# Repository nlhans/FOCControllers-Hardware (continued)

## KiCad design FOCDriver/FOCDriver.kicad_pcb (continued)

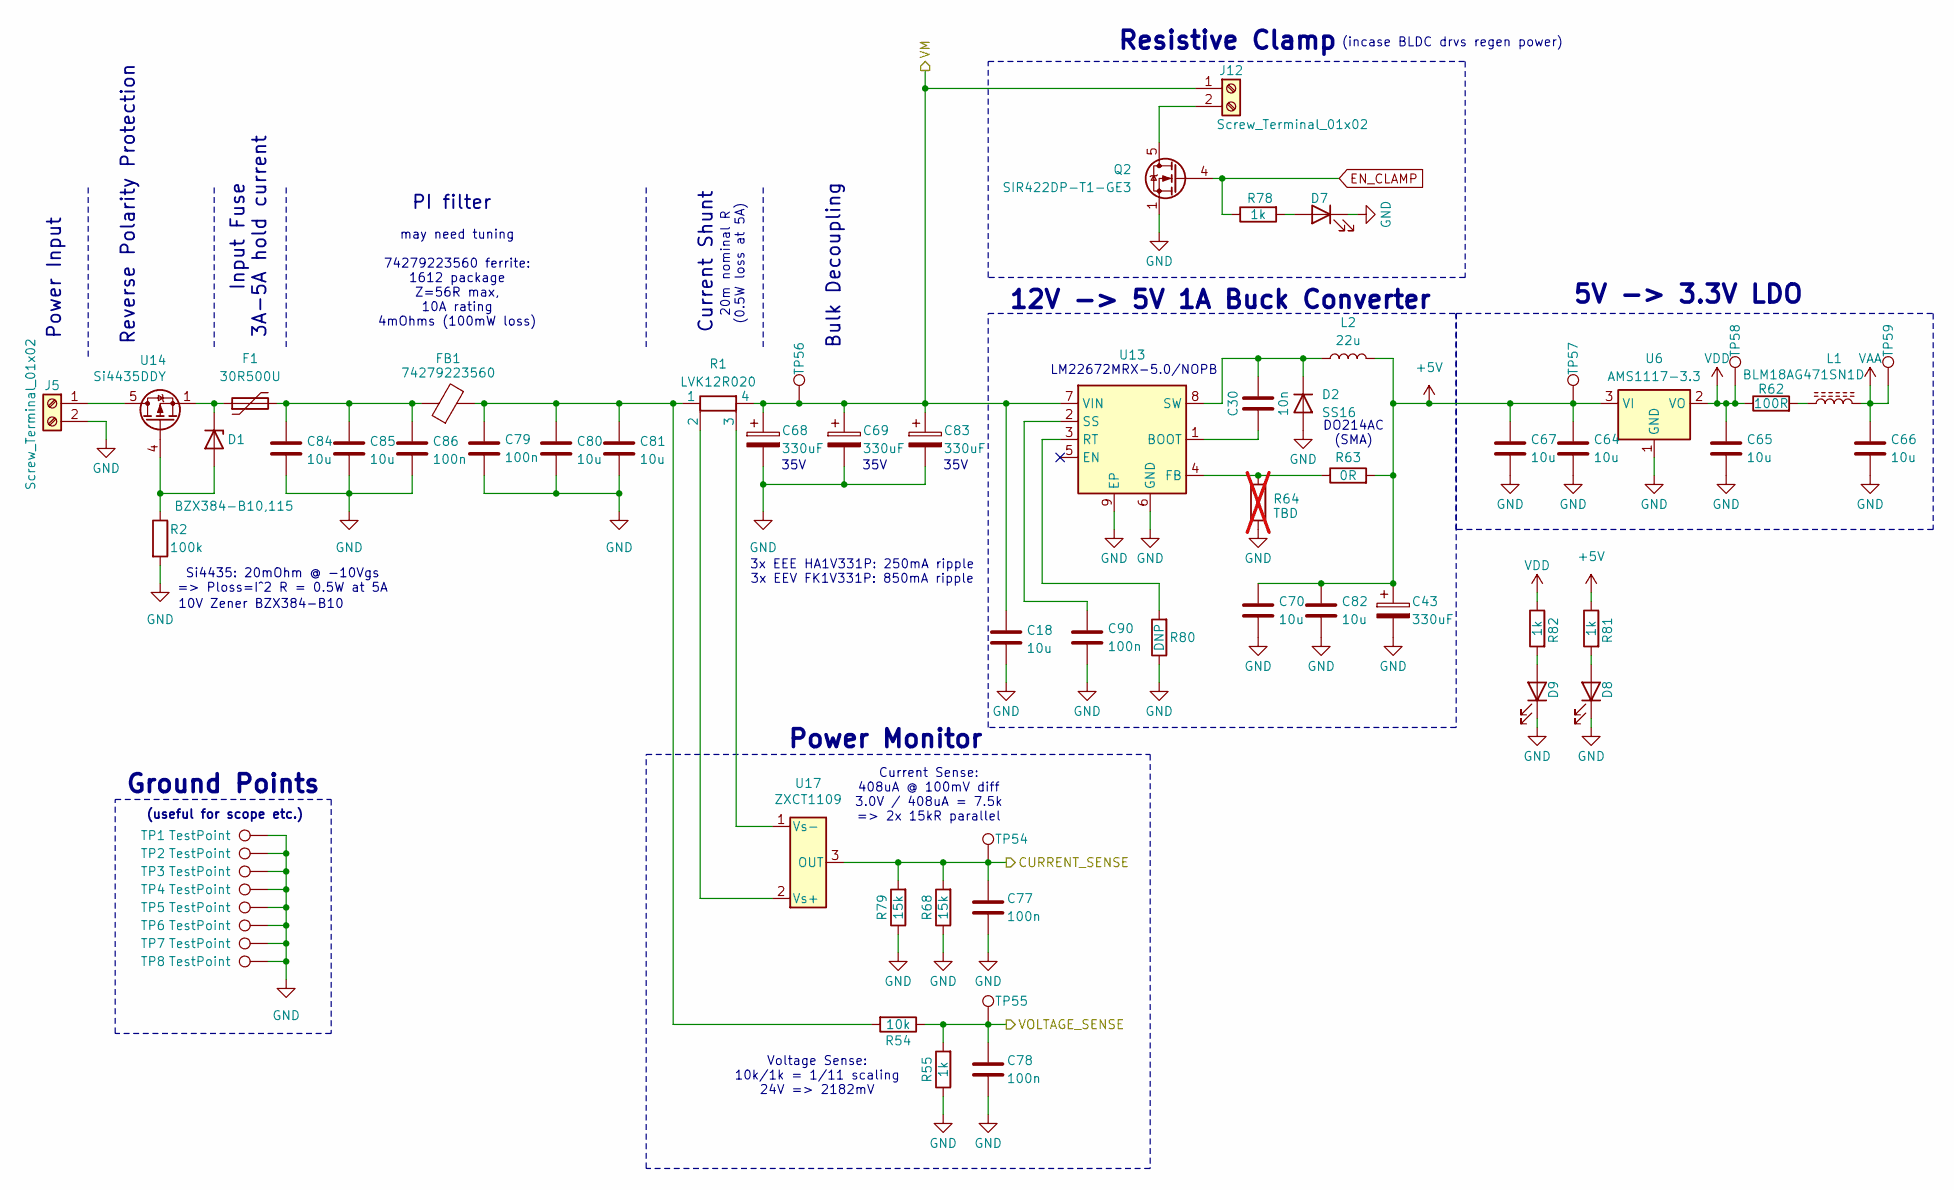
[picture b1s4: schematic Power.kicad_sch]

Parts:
C18, C64, C65, C66, C67, C70, C80, C81, C82, C84, C85: 10u; C_1206_3216Metric
C30: 10n; Nice_0603C
C43: 330uF; CP_Elec_8x10.5; MPN EEEFT1V331AP
C68, C69, C83: 330uF; CP_Elec_10x10.5; MPN EEV FK1V331P
C77, C78: 100n; Nice_0402C
C79, C86, C90: 100n; Nice_0603C
D1: BZX384-B10,115; D_SOD-323_HandSoldering; MPN BZX384-B10,115
D2: SS16; D_SMA
D7, D8, D9: APT2012SYCK; LED_0805_2012Metric; MPN APT2012SYCK
F1: 30R500U; LIttelfuse_30R
FB1: 74279223560; L_1812_4532Metric
J5, J12: Screw_Terminal_01x02; TerminalBlock_Phoenix_MKDS-1,5-2_1x02_P5.00mm_Horizontal
L1: BLM18AG471SN1D; L_0805_2012Metric
L2: 22u; L_Bourns-SRN8040_8x8.15mm; MPN SRN8040-220M
Q2: SIR422DP-T1-GE3; PowerPAK_SO-8_Single
R1: LVK12R020; R_Shunt_Ohmite_LVK12; MPN LVK12R020CER
R2: 100k; Nice_0402R
R54: 10k; Nice_0402R
R55, R78, R81, R82: 1k; Nice_0402R
R62: 100R; Nice_0402R
R63: 0R; Nice_0402R
R64: TBD; Nice_0402DNP; not fitted
R68, R79: 15k; Nice_0402R
R80: DNP; Nice_0402DNP
TP1, TP2, TP3, TP4, TP5, TP6, TP7, TP8: TestPoint; TestPoint_THTPad_D1.0mm_Drill0.5mm
TP54, TP55, TP56, TP57, TP58, TP59: TestPoint; TP_0.6mm
U6: AMS1117-3.3; SOT-223-3_TabPin2
U13: LM22676MR-5; TI_SO-PowerPAD-8; MPN LM22672MRX-5.0/NOPB
U14: Si4435DDY; SOIC-8_3.9x4.9mm_P1.27mm
U17: ZXCT1109; SOT-23; MPN ZXCT1109SA-7

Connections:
+5V: C43.1, C64.1, C67.1, C70.1, C82.1, L2.2, R63.2, R81.1, TP57.1, U6.3 (VI); also elsewhere on the board
/MCU/AIN_I: C77.1, R68.2, R79.2, TP54.1, U17.3 (OUT); also elsewhere on the board
/MCU/AIN_V: C78.1, R54.1, R55.2, TP55.1; also elsewhere on the board
/Motor1/VM: C18.1, C68.1, C69.1, C83.1, J12.1, R1.4, TP56.1, U13.7 (VIN); also elsewhere on the board
EN_CLAMP: Q2.4 (G), R78.1; also elsewhere on the board
GND: C18.2, C43.2, C64.2, C65.2, C66.2, C67.2, C68.2, C69.2, C70.2, C77.2, C78.2, C79.2, C80.2, C81.2, C82.2, C83.2, C84.2, C85.2, C86.2, C90.2, D2.2 (A), D7.1 (K), D8.1 (K), D9.1 (K), J5.2, Q2.1 (S), Q2.2 (S), Q2.3 (S), R2.2, R55.1, R64.2, R68.1, R79.1, R80.1, TP1.1, TP2.1, TP3.1, TP4.1, TP5.1, TP6.1, TP7.1, TP8.1, U6.1 (GND), U13.6 (GND), U13.9 (EP); also elsewhere on the board
unnamed: C79.1, C80.1, C81.1, FB1.2, R1.1, R54.2
unnamed: C84.1, C85.1, C86.1, F1.2, FB1.1
unnamed: D1.2 (A), R2.1, U14.4 (G)
unnamed: D1.1 (K), F1.1, U14.1 (S), U14.2 (S), U14.3 (S)
unnamed: C30.2, D2.1 (K), L2.1, U13.8 (SW)
unnamed: D7.2 (A), R78.2
unnamed: D8.2 (A), R81.2
unnamed: D9.2 (A), R82.2
unnamed: J5.1, U14.5 (D), U14.6 (D), U14.7 (D), U14.8 (D)
unnamed: J12.2, Q2.5 (D)
unnamed: L1.1, R62.2
unnamed: C30.1, U13.1 (BOOT)
unnamed: R63.1, R64.1, U13.4 (FB)
unnamed: R80.2, U13.3 (RT)
unnamed: C90.1, U13.2 (SS)
unnamed: R1.2, U17.2 (Vs+)
unnamed: R1.3, U17.1 (Vs-)
VAA: C66.1, L1.2, TP59.1; also elsewhere on the board
VDD: C65.1, R62.1, R82.1, TP58.1, U6.2 (VO); also elsewhere on the board

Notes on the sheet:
(useful for scope etc.)
Current Shunt
DO214AC (SMA)
may need tuning 74279223560 ferrite: 1612 package Z=56R max, 10A rating 4mOhms (100mW loss)
35V
3x EEE HA1V331P: 250mA ripple 3x EEV FK1V331P: 850mA ripple
(incase BLDC drvs regen power)
Power Input
Input Fuse 3A-5A hold current
Resistive Clamp
Power Monitor
LM22672MRX-5.0/NOPB
Bulk Decoupling
Ground Points
10V Zener BZX384-B10
12V -> 5V 1A Buck Converter
Voltage Sense: 10k/1k = 1/11 scaling 24V => 2182mV
Si4435: 20mOhm @ -10Vgs => Ploss=I^2 R = 0.5W at 5A
5V -> 3.3V LDO
PI filter
20m nominal R (0.5W loss at 5A)
Reverse Polarity Protection
Current Sense: 408uA @ 100mV diff 3.0V / 408uA = 7.5k => 2x 15kR parallel

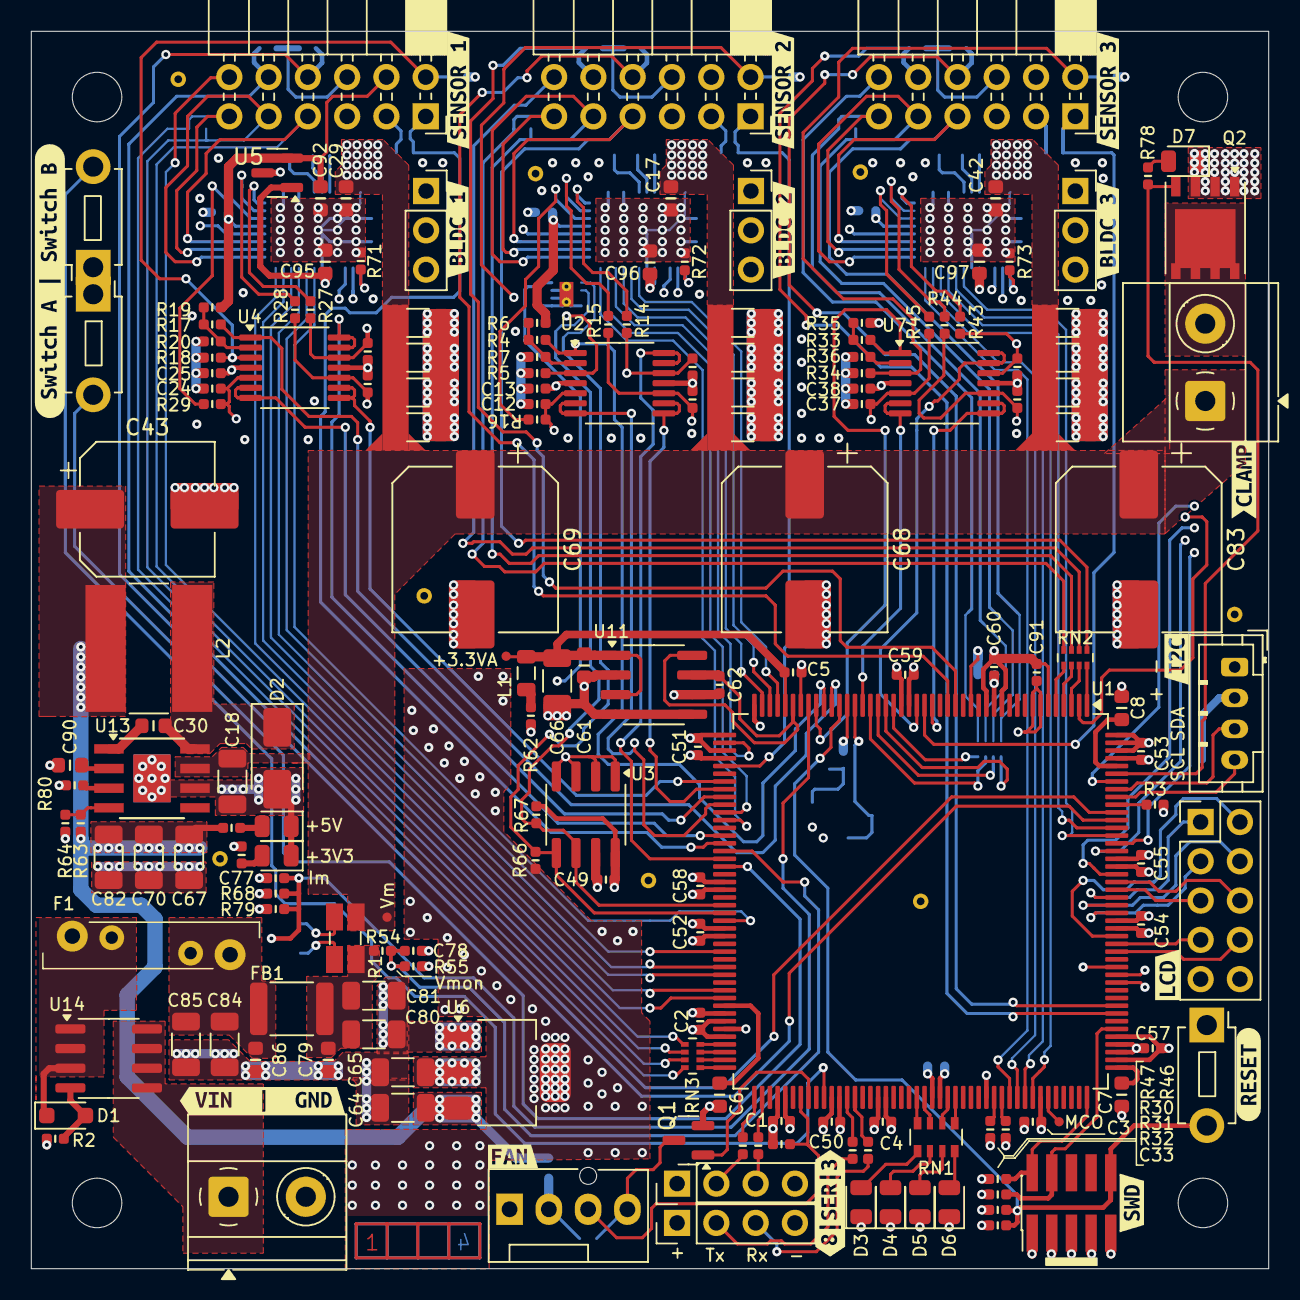
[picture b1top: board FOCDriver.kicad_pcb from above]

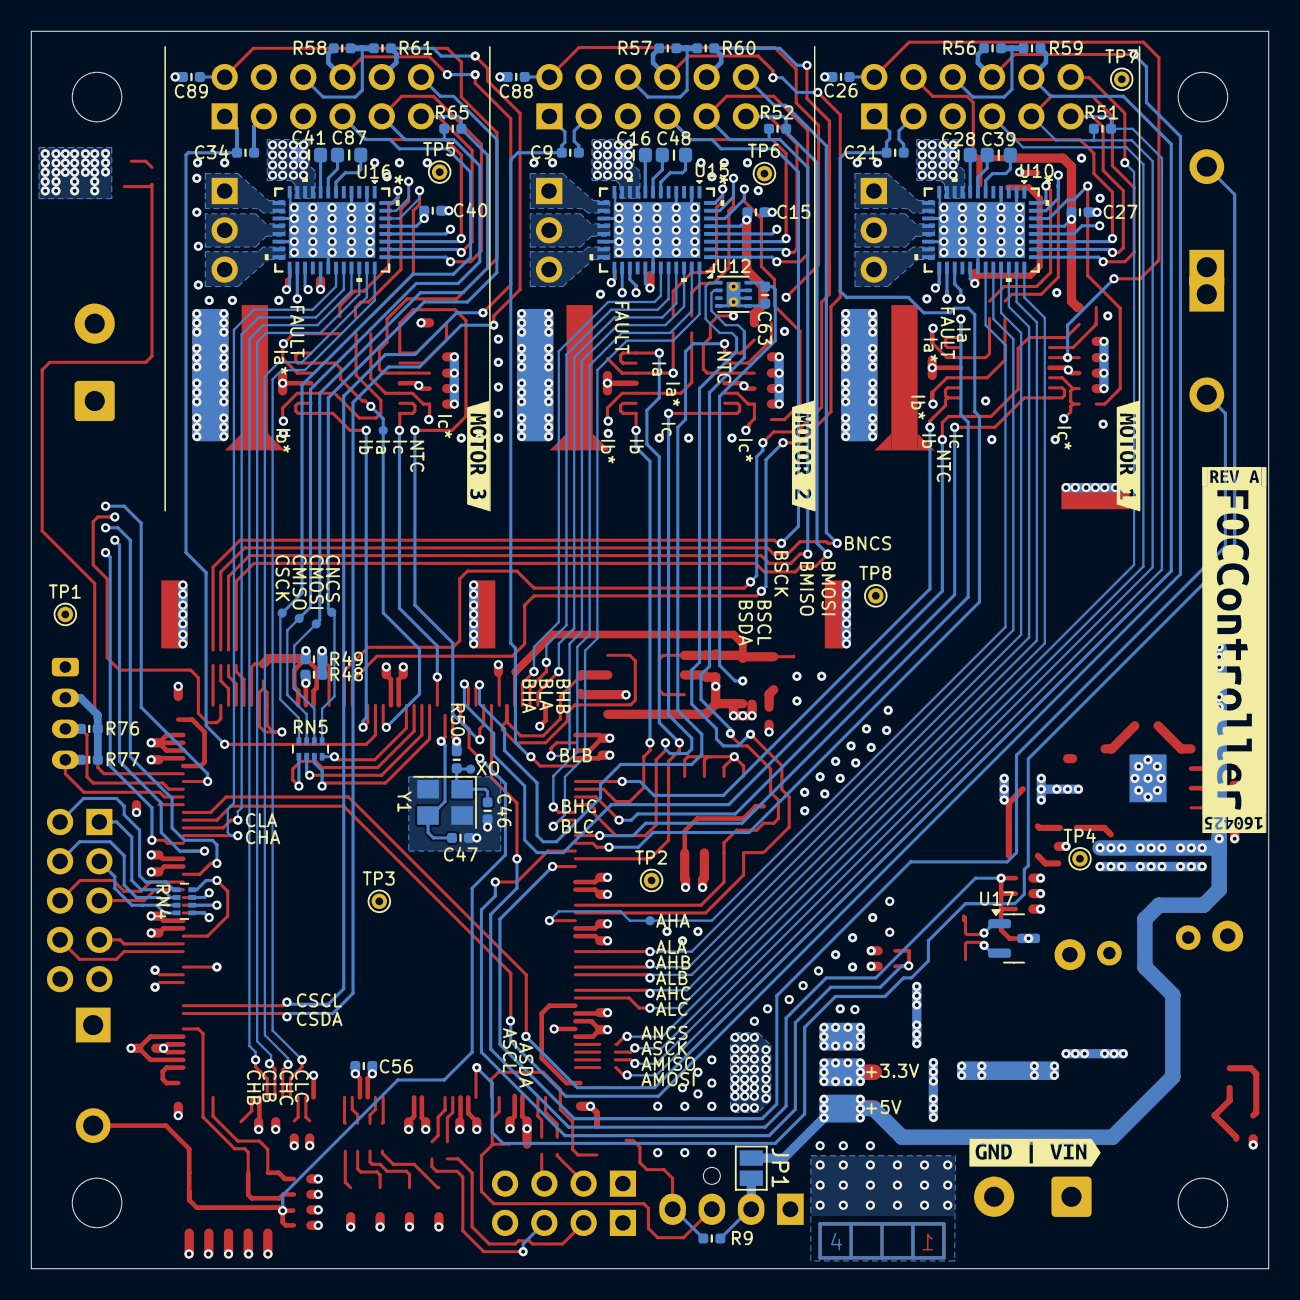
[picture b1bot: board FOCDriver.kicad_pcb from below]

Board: 4 copper layers, 80.0 x 80.0 mm, 318 parts (124 on the bottom side), 198 nets.

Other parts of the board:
kibuzzard-67EC00B3: G***; kibuzzard-67EC00B3
kibuzzard-67ED282B: G***; kibuzzard-67ED282B
kibuzzard-67F3CA67: G***; kibuzzard-67F3CA67
kibuzzard-67F3CAB6: G***; kibuzzard-67F3CAB6
kibuzzard-67F3CB42: G***; kibuzzard-67F3CB42
kibuzzard-67F3CD14: G***; kibuzzard-67F3CD14
kibuzzard-67F3CD28: G***; kibuzzard-67F3CD28
kibuzzard-67F3CD42: G***; kibuzzard-67F3CD42
kibuzzard-67F3CD48: G***; kibuzzard-67F3CD48
kibuzzard-67F3CD55: G***; kibuzzard-67F3CD55
kibuzzard-67F3CD63: G***; kibuzzard-67F3CD63
kibuzzard-67F3FE9D: G***; kibuzzard-67F3FE9D
kibuzzard-67F3FEBC: G***; kibuzzard-67F3FEBC
kibuzzard-67F3FEF2: G***; kibuzzard-67F3FEF2
kibuzzard-67F3FF37: G***; kibuzzard-67F3FF37
kibuzzard-67F6A3C3: G***; kibuzzard-67F6A3C3
kibuzzard-67F56438: G***; kibuzzard-67F56438
kibuzzard-67FA2A95: G***; kibuzzard-67FA2A95
kibuzzard-67FA3F2F: G***; kibuzzard-67FA3F2F
kibuzzard-67FE68DD: G***; kibuzzard-67FE68DD
kibuzzard-67FE6936: G***; kibuzzard-67FE6936
kibuzzard-67FE6963: G***; kibuzzard-67FE6963

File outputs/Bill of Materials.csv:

"Id";"Designator";"Footprint";"Quantity";"Designation";"Supplier and ref";
1;"R82,R81,R67,R78,R55,R66,R56,R59,R60,R76,R61,R58,R77,R57";"Nice_0402R";14;"1k";;;
2;"D9,D8,D6,D5,D7,D3,D4";"LED_0805_2012Metric";7;"APT2012SYCK";;;
3;"C97,C96,C95,C92,C8,C6,C7";"Nice_0603C";7;"2.2u";;;
4;"R68,R79";"Nice_0402R";2;"15k";;;
5;"R19,R5,R34,R32,R35,R8,R36,R4,R6,R7,R20,R54,R33,R31,R3,R17,R18,R30,R9";"Nice_0402R";19;"10k";;;
6;"TP54,TP56,TP53,TP59,TP55,TP22,TP75,TP47,TP36,TP49,TP70,TP69,TP41,TP74,TP35,TP23,TP12,TP20,TP24,TP66,TP31,TP40,TP32,TP48,TP76,TP39,TP17,TP43,TP65,TP16,TP34,TP64,TP63,TP71,TP25,TP61,TP58,TP51,TP15,TP73,TP52,TP33,TP10,TP68,TP42,TP14,TP28,TP29,TP77,TP38,TP26,TP45,TP44,TP11,TP72,TP13,TP46,TP62,TP30,TP21,TP57,TP37,TP67,TP19,TP60,TP27,TP50,TP18";"TP_0.6mm";68;"TestPoint";;;
7;"C50,C91,C25,C51,C3,C49,C57,C77,C78,C33,C2,C55,C54,C60,C5,C4,C13,C53,C58,C59,C52,C1,C38,C56,C40,C9,C89,C34,C15,C88,C27,C21,C63,C26";"Nice_0402C";34;"100n";;;
8;"R44,R29,R15,R27,R45,R43,R14,R28,R16";"Nice_0402R";9;"820R";;;
9;"J12,J5";"TerminalBlock_Phoenix_MKDS-1,5-2_1x02_P5.00mm_Horizontal";2;"Screw_Terminal_01x02";;;
10;"C72,C31,C20,C74,C85,C19,C18,C84,C66,C80,C70,C75,C65,C71,C82,C76,C67,C81,C44,C73,C45,C64,C32";"C_1206_3216Metric";23;"10u";;;
11;"R2";"Nice_0402R";1;"100k";;;
12;"SW3,SW2,SW1";"SW_PUSH_1P1T_6x3.5mm_H5.0_APEM_MJTP1250";3;"SW_Push";;;
13;"R71,R47,R46,R73,R63,R72,R49";"Nice_0402R";7;"0R";;;
14;"U2,U4,U7";"TSSOP-14_4.4x5mm_P0.65mm";3;"LM324";;;
15;"J11,J9";"PinHeader_1x04_P2.54mm_Vertical";2;"Conn_01x04";;;
16;"R69,R75,R62,R74,R70";"Nice_0402R";5;"100R";;;
17;"J4";"PinHeader_2x05_P2.54mm_Vertical";1;"Conn_02x05_Odd_Even";;;
18;"R1";"R_Shunt_Ohmite_LVK12";1;"LVK12R020";;;
19;"U3";"SOIC-8_3.9x4.9mm_P1.27mm";1;"24LC64";;;
20;"SWD1";"PinHeader_2x05_P1.27mm_Vertical_SMD";1;"Conn_02x05_Odd_Even";;;
21;"C11,C12,C35,C23,C36,C37,C22,C10,C24";"Nice_0402C";9;"100p";;;
22;"R80";"Nice_0402DNP";1;"DNP";;;
23;"U6";"SOT-223-3_TabPin2";1;"AMS1117-3.3";;;
24;"C86,C79,C90,C42,C17,C29";"Nice_0603C";6;"100n";;;
25;"J8,J7,J6";"PinSocket_1x03_P2.54mm_Vertical";3;"Conn_01x03_Pin";;;
26;"M1";"FanPinHeader_1x04_P2.54mm_Vertical";1;"Fan_Tacho_PWM";;;
27;"FB1";"L_1812_4532Metric";1;"74279223560";;;
28;"J1,J3,J2";"PinSocket_2x06_P2.54mm_Horizontal";3;"Conn_02x06_Odd_Even";;;
29;"RN1";"R_Array_Convex_4x0603";1;"EXB-38V102JV";;;
30;"RN2,RN3,RN4,RN5";"R_Array_Concave_4x0402";4;"EXB-N8N220JX";;;
31;"Q1";"SOT-23";1;"2N7002";;;
32;"L2";"L_Bourns-SRN8040_8x8.15mm";1;"22u";;;
33;"C69,C68,C83";"CP_Elec_10x10.5";3;"330uF";;;
34;"C61,C28,C16,C41";"Nice_0603C";4;"1u";;;
35;"C30";"Nice_0603C";1;"10n";;;
36;"U11";"SOIC-8_3.9x4.9mm_P1.27mm";1;"MCP1501-25E/SN";;;
37;"U1";"LQFP-176_24x24mm_P0.5mm";1;"STM32H725IGTx";;;
38;"F1";"LIttelfuse_30R";1;"30R500U";;;
39;"R64,R48";"Nice_0402DNP";2;"TBD";;;
40;"D2";"D_SMA";1;"SS16";;;
41;"L1";"L_0805_2012Metric";1;"BLM18AG471SN1D";;;
42;"C43";"CP_Elec_8x10.5";1;"330uF";;;
43;"U14";"SOIC-8_3.9x4.9mm_P1.27mm";1;"Si4435DDY";;;
44;"U13";"TI_SO-PowerPAD-8";1;"LM22676MR-5";;;
45;"J10";"JST_PH_B4B-PH-K_1x04_P2.00mm_Vertical";1;"Conn_01x04";;;
46;"D1";"D_SOD-323_HandSoldering";1;"BZX384-B10,115";;;
47;"Q2";"PowerPAK_SO-8_Single";1;"SIR422DP-T1-GE3";;;
48;"U5";"SOT-23";1;"AP7375-30SA-7";;;
49;"C62";"Nice_0402C";1;"1n";;;
50;"Y1";"Crystal_SMD_3225-4Pin_3.2x2.5mm";1;"ECS-250-18-33-JGN-TR3";;;
51;"U16,U10,U15";"VQFN40_RGF_TEX";3;"DRV8316CR";;;
52;"U12";"WSON-8-1EP_2x2mm_P0.5mm_EP0.9x1.6mm_ThermalVias";1;"TMP1075DSG";;;
53;"C39,C48,C87";"Nice_0603C";3;"47n";;;
54;"U17";"SOT-23";1;"ZXCT1109";;;
55;"R65,R51,R50,R52";"Nice_0402R";4;"470R";;;
56;"TP6,TP1,TP4,TP7,TP2,TP5,TP8,TP3";"TestPoint_THTPad_D1.0mm_Drill0.5mm";8;"TestPoint";;;
57;"C46,C47";"Nice_0402C";2;"18p";;;

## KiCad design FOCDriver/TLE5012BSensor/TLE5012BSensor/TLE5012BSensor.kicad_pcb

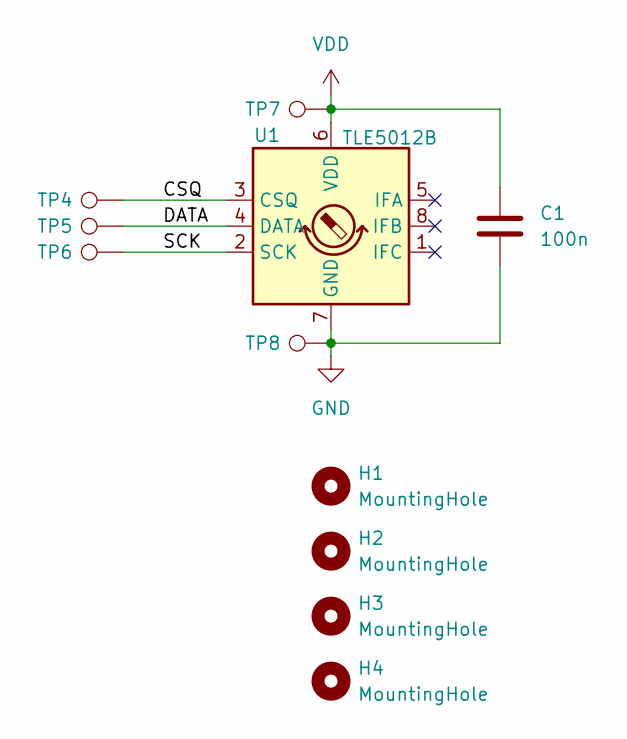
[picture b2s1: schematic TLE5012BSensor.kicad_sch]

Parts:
C1: 100n; Nice_0603C
H1, H2, H3, H4: MountingHole; MountingHole_3.2mm_M3
TP4, TP5, TP6, TP7, TP8: TestPoint; TestPoint_Pad_1.0x1.0mm
U1: TLE5012B; SOIC-8_3.9x4.9mm_P1.27mm

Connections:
/CSQ: TP4.1, U1.3 (CSQ)
/DATA: TP5.1, U1.4 (DATA)
/SCK: TP6.1, U1.2 (SCK)
GND: C1.2, TP8.1, U1.7 (GND)
VDD: C1.1, TP7.1, U1.6 (VDD)

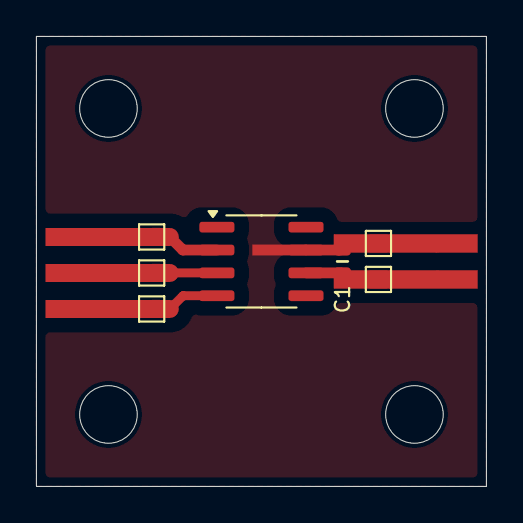
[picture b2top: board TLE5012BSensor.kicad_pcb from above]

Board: 2 copper layers, 25.0 x 25.0 mm, 11 parts (0 on the bottom side), 5 nets.

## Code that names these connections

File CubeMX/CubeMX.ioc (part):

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Mcu.Name=STM32H725IGTx
Mcu.Package=LQFP176
Mcu.UserName=STM32H725IGTx
PA0.Signal=S_TIM5_CH1
PA1.Signal=S_TIM5_CH2
PA13(JTMS/SWDIO).Mode=Serial_Wire
PA13(JTMS/SWDIO).Signal=DEBUG_JTMS-SWDIO
PA14(JTCK/SWCLK).Mode=Serial_Wire
PA14(JTCK/SWCLK).Signal=DEBUG_JTCK-SWCLK
PA2.Signal=S_TIM5_CH3
PA3.Signal=S_TIM5_CH4
PA4.Signal=ADCx_INP18
PA5.Signal=S_TIM2_CH1_ETR
PA6.Signal=ADCx_INP3
PA7.Signal=ADCx_INP7
PA8.Mode=Clock-out-1
PA8.Signal=RCC_MCO_1
PB0.Signal=S_TIM3_CH3
PB1.Signal=S_TIM3_CH4
PB10.Signal=S_TIM2_CH3
PB11.Signal=S_TIM2_CH4
PB12.Mode=NSS_Signal_Hard_Output
PB12.Signal=SPI2_NSS
PB13.Mode=Full_Duplex_Master
PB13.Signal=SPI2_SCK
PB14.Mode=Full_Duplex_Master
PB14.Signal=SPI2_MISO
PB15.Mode=Full_Duplex_Master
PB15.Signal=SPI2_MOSI
PB3(JTDO/TRACESWO).Signal=GPIO_Output
PB4(NJTRST).Signal=S_TIM3_CH1
PB5.Signal=S_TIM3_CH2
PB6.Mode=I2C
PB6.Signal=I2C1_SCL
PB7.Mode=I2C
PB7.Signal=I2C1_SDA
PB8.Mode=I2C
PB8.Signal=I2C4_SCL
PB9.Mode=I2C
PB9.Signal=I2C4_SDA
PC0.Signal=ADCx_INP10
PC1.Signal=ADCx_INP11
PC10.Mode=I2C
PC10.Signal=I2C5_SDA
PC11.Mode=I2C
PC11.Signal=I2C5_SCL
PC2_C.Mode=IN0-Single-Ended
PC2_C.Signal=ADC3_INP0
PC3_C.Mode=IN1-Single-Ended
PC3_C.Signal=ADC3_INP1
PC4.Signal=ADCx_INP4
PC5.Signal=ADCx_INP8
PC6.Signal=S_TIM8_CH1
PC7.Signal=S_TIM8_CH2
PC8.Signal=S_TIM8_CH3
PC9.Signal=S_TIM8_CH4
PD12.Signal=GPIO_Input
PD13.Signal=S_TIM4_CH2
PD15.Signal=GPIO_Output
PD5.Signal=GPIO_Output
PD6.Signal=GPIO_Output
PD7.Mode=Full_Duplex_Master
PD7.Signal=SPI1_MOSI
PD8.Mode=Asynchronous
PD8.Signal=USART3_TX
PD9.Mode=Asynchronous
PD9.Signal=USART3_RX
PE0.Signal=GPIO_Input
PE1.Signal=GPIO_Output
PE11.Signal=S_TIM1_CH2
PE13.Signal=S_TIM1_CH3
PE14.Signal=S_TIM1_CH4
PE2.Mode=Full_Duplex_Master
PE2.Signal=SPI4_SCK
PE4.Mode=NSS_Signal_Hard_Output
PE4.Signal=SPI4_NSS
PE5.Mode=Full_Duplex_Master
PE5.Signal=SPI4_MISO
PE6.Mode=Full_Duplex_Master
PE6.Signal=SPI4_MOSI
PE7.Signal=GPIO_Output
PE8.Signal=GPIO_Output
PE9.Signal=S_TIM1_CH1
PF0.Mode=I2C
PF0.Signal=I2C2_SDA
PF1.Mode=I2C
PF1.Signal=I2C2_SCL
PF10.Mode=IN6-Single-Ended
PF10.Signal=ADC3_INP6
PF11.Mode=IN2-Single-Ended
PF11.Signal=ADC1_INP2
PF12.Mode=IN6-Single-Ended
PF12.Signal=ADC1_INP6
PF13.Mode=IN2-Single-Ended
PF13.Signal=ADC2_INP2
PF14.Mode=IN6-Single-Ended
PF14.Signal=ADC2_INP6
PF15.Signal=GPIO_Input
PF3.Mode=IN5-Single-Ended
PF3.Signal=ADC3_INP5
PF4.Mode=IN9-Single-Ended
PF4.Signal=ADC3_INP9
PF5.Mode=IN4-Single-Ended
PF5.Signal=ADC3_INP4
PF6.Mode=NSS_Signal_Hard_Output
PF6.Signal=SPI5_NSS
PF7.Mode=Full_Duplex_Master
PF7.Signal=SPI5_SCK
PF8.Mode=Full_Duplex_Master
PF8.Signal=SPI5_MISO
PF9.Mode=Full_Duplex_Master
PF9.Signal=SPI5_MOSI
PG10.Mode=NSS_Signal_Hard_Output
PG10.Signal=SPI1_NSS
PG11.Mode=Full_Duplex_Master
PG11.Signal=SPI1_SCK
PG12.Signal=GPIO_Output
PG13.Signal=GPIO_Output
PG14.Signal=GPIO_Input
PG15.Signal=GPIO_Input
PG2.Signal=GPIO_Output
PG3.Signal=GPIO_Output
PG4.Signal=GPIO_Output
PG5.Signal=GPIO_Output
PG9.Mode=Full_Duplex_Master
PG9.Signal=SPI1_MISO
PH0-OSC_IN.Mode=HSE-External-Oscillator
PH0-OSC_IN.Signal=RCC_OSC_IN
PH1-OSC_OUT.Mode=HSE-External-Oscillator
PH1-OSC_OUT.Signal=RCC_OSC_OUT
PJ8.Mode=Asynchronous
PJ8.Signal=UART8_TX
PJ9.Mode=Asynchronous
PJ9.Signal=UART8_RX
RCC.SYSCLKFreq_VALUE=550000000
RCC.SYSCLKSource=RCC_SYSCLKSOURCE_PLLCLK
board=custom

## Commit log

2025-04-21 Sensor PCB fixes labels
2025-04-21 Untented vias for DRVOFF signal Added unallocated IOs for DRVOFF potentially
2025-04-21 Ordered at Aisler
2025-08-28 Bill of materials
